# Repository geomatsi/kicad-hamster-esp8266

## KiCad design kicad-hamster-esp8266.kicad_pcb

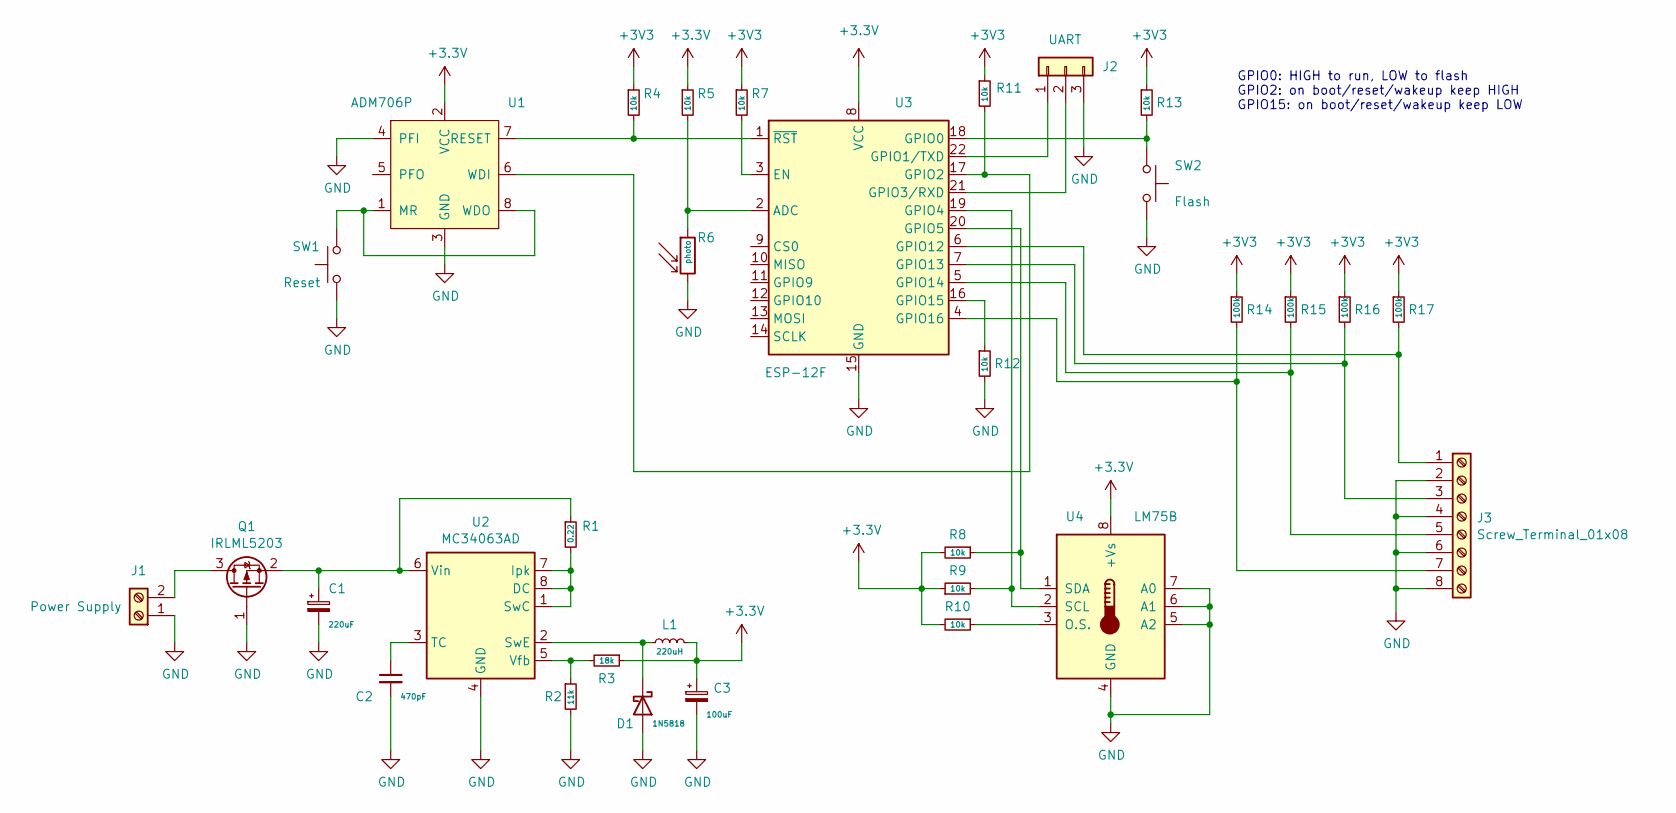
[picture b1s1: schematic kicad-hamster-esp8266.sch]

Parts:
C1: 220uF; CP_Radial_D8.0mm_P3.80mm
C2: 470pF; C_1206_3216Metric_Pad1.42x1.75mm_HandSolder
C3: 100uF; CP_Radial_D8.0mm_P3.80mm
D1: 1N5818; D_DO-41_SOD81_P10.16mm_Horizontal
J1: Power Supply; TerminalBlock_Phoenix_MKDS-1,5-2_1x02_P5.00mm_Horizontal
J2: UART; PinHeader_1x03_P2.54mm_Vertical
J3: Screw_Terminal_01x08; TerminalBlock_Phoenix_MKDS-1,5-8_1x08_P5.00mm_Horizontal
L1: 220uH; L_Radial_D7.2mm_P3.00mm_MuRATA_1700
Q1: IRLML5203; SOT-23
R1: 0.22; R_1206_3216Metric_Pad1.42x1.75mm_HandSolder
R2: 11k; R_1206_3216Metric_Pad1.42x1.75mm_HandSolder
R3: 18k; R_1206_3216Metric_Pad1.42x1.75mm_HandSolder
R4, R5, R7, R8, R9, R10, R11, R12, R13: 10k; R_1206_3216Metric_Pad1.42x1.75mm_HandSolder
R6: photo; CP_Radial_D8.0mm_P3.80mm
R14, R15, R16, R17: 100k; R_1206_3216Metric_Pad1.42x1.75mm_HandSolder
SW1: Reset; SW_SPST_REED_CT05-XXXX-J1
SW2: Flash; PinHeader_1x02_P2.54mm_Vertical
U1: ADM706P; SOIC-8_3.9x4.9mm_P1.27mm
U2: MC34063AD; SOIC-8_3.9x4.9mm_P1.27mm
U3: ESP-12F; ESP-12E
U4: LM75B; SOIC-8_3.9x4.9mm_P1.27mm

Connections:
GND: C1.2, C2.2, C3.2, D1.2 (A), J1.1, J2.3, J3.2, J3.4, J3.6, J3.8, Q1.1 (G), R2.2, R6.2, R12.2, SW1.1, SW2.2, U1.3 (GND), U1.4 (PFI), U2.4 (GND), U3.15 (GND), U4.4 (GND), U4.5 (A2), U4.6 (A1), U4.7 (A0)
unnamed: C1.1, Q1.2 (S), R1.1, U2.6 (Vin)
unnamed: C2.1, U2.3 (TC)
unnamed: D1.1 (K), L1.1, U2.2 (SwE)
unnamed: J1.2, Q1.3 (D)
unnamed: J2.1, U3.22 (GPIO1/TXD)
unnamed: J2.2, U3.21 (GPIO3/RXD)
unnamed: J3.1, R17.2, U3.6 (GPIO12)
unnamed: J3.3, R16.2, U3.7 (GPIO13)
unnamed: J3.5, R15.2, U3.5 (GPIO14)
unnamed: J3.7, R14.2, U3.4 (GPIO16)
unnamed: R1.2, U2.1 (SwC), U2.7 (Ipk), U2.8 (DC)
unnamed: R2.1, R3.2, U2.5 (Vfb)
unnamed: R4.2, U1.7 (RESET), U3.1 (~RST)
unnamed: R5.2, R6.1, U3.2 (ADC)
unnamed: R7.2, U3.3 (EN)
unnamed: R8.1, U3.20 (GPIO5), U4.1 (SDA)
unnamed: R9.2, U3.19 (GPIO4), U4.2 (SCL)
unnamed: R10.1, U4.3 (O.S.)
unnamed: R11.2, U1.6 (WDI), U3.17 (GPIO2)
unnamed: R12.1, U3.16 (GPIO15)
unnamed: R13.2, SW2.1, U3.18 (GPIO0)
unnamed: SW1.2, U1.1 (MR), U1.8 (WDO)

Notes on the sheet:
GPIO0: HIGH to run, LOW to flash GPIO2: on boot/reset/wakeup keep HIGH GPIO15: on boot/reset/wakeup keep LOW

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
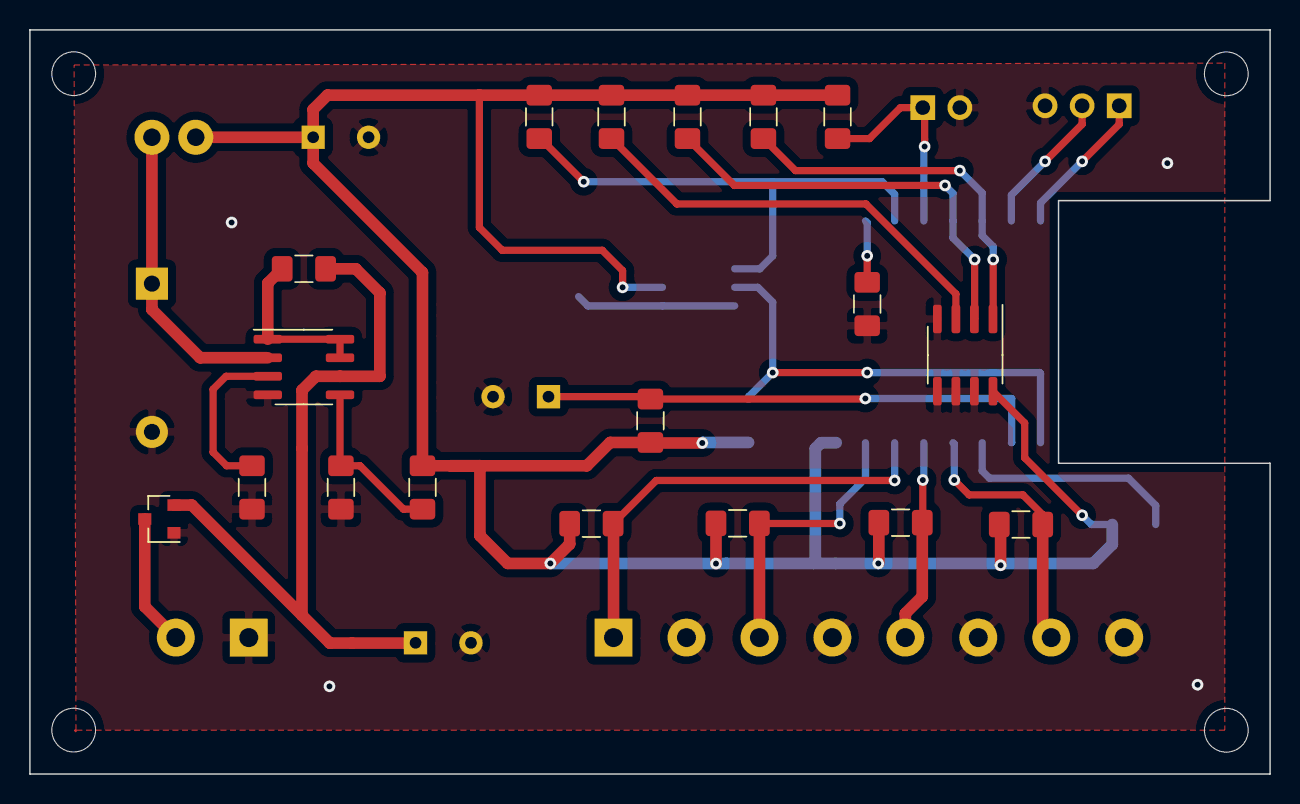
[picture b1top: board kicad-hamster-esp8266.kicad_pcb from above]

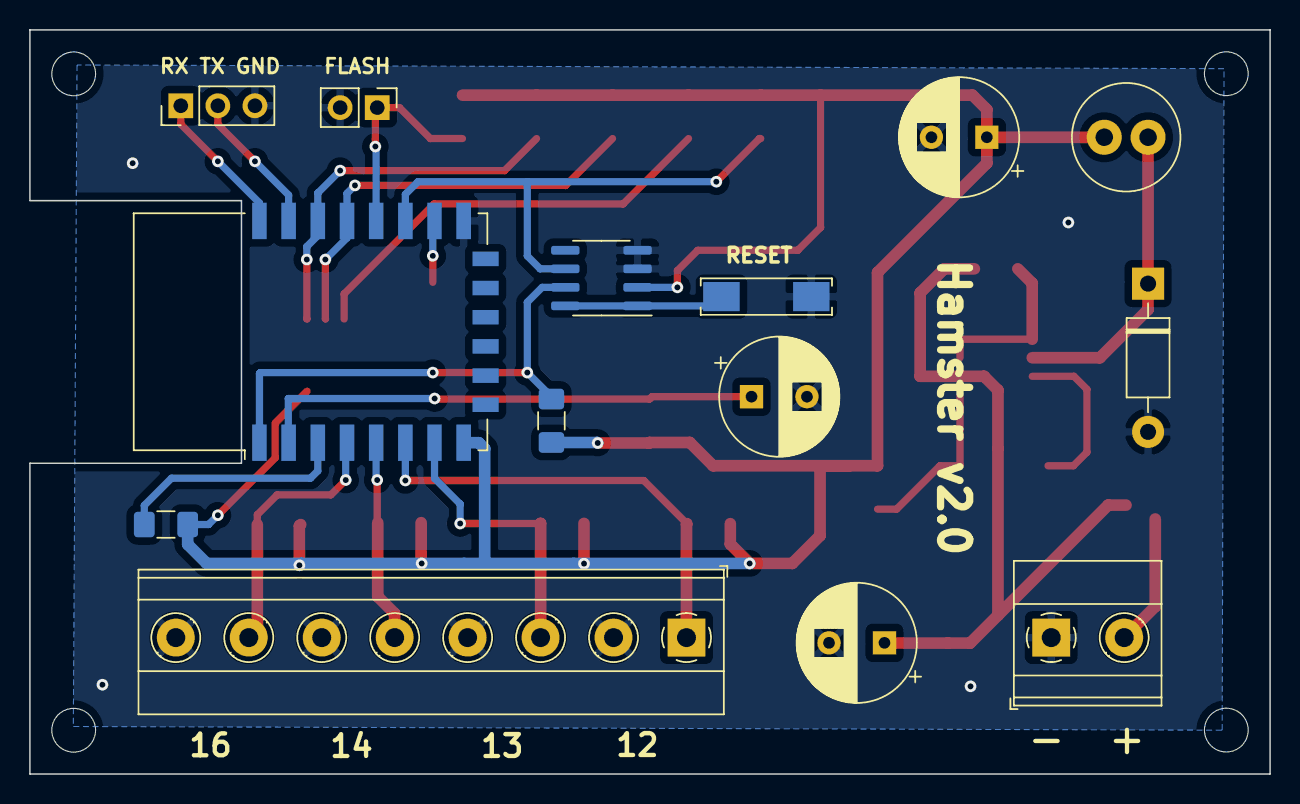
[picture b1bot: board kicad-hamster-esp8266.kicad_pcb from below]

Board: 2 copper layers, 85.0 x 51.0 mm, 32 parts (14 on the bottom side), 24 nets.

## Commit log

2020-07-09 hamster v2: esp8266 board
    Schematics stage I: esp12F and power supply circuitry.
2020-07-12 hamster v2 esp8266: flash/reset circuitry
    Draw flash/reset/enable circuitry including control pins and
    specific gpio pins.
2020-07-12 hamster v2 esp8266: reed switch circuitry
    Draw reed switch circuitry
2020-07-16 hamster v2 esp8266: add pull-ups and pull-downs
    Add pull up/down resistors for major ESP pins based
    on experiments with prototype board.
2020-07-18 Add LM75A i2c temperature sensor
2020-07-18 add external watchdog circuit
2020-07-19 ADC: add photoresistor circuitry
2020-07-20 pcb: net list and preliminary placement
2020-07-22 pcb: first layout version
2020-07-26 pcb: text and updated footprint
    - modify footprint of reed switch connector
    - add silkscreen text
2020-07-26 generate gerber files
2020-07-26 update legend and gerbers
    - add reed switch connector legend
    - regenerate gerbers
